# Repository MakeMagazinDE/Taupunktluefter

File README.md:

Maker Media GmbH

***

# Taupunktlüfter

**Lüften ist die beste und billigste Maßnahme gegen feuchte Keller  – jedenfalls, wenn man es richtig macht und sich nicht von außen zusätzliche Nässe ins Gewölbe holt. Bei unserem Projekt behält ein Arduino Nano die aktuellen Taupunkte drinnen und draußen rund um die Uhr im Auge und legt durch gezieltes Lüften den Keller trocken.**

Hier gibt es den Arduino-Code zum Projekt des Taupunktlüfters sowohl in der Fassung ohne Datenlogger (Code im Ordner _Taupunkt_Lueftung_), wie in Make 1/22 beschrieben, als auch in der Fassung mit Datenlogger (Code im Ordner _Taupunkt_Lueftung_Datenlogging_Version_2.13_), die in Make 2/22 beschrieben wird. Diese Version zeigt auch der erweiterte Schaltplan:

Der im Schaltplan gezeigte _Modusschalter_ ist ein Schalter mit drei Schaltstellungen: links, Mitte, rechts. In der Mittelstellung sind alle Pole frei, bei rechts wird der mittlere Pol nach rechts verbunden und bei links der mittlere Pol nach links. Beschaltet wird dann beispielsweise so: linker Kontakt des Schalters auf GND (linke Stellung ist dann für **aus**), rechter Kontakt auf VCC (5V, rechte Stellung ist dann für **an**) und Mittelkontakt auf Arduino-IO-Pin 6 (Verbindung zum Relais, Mittelstellung ist dann für **Automatik**).

Die wichtigsten Fragen rund um den Taupunktlüfter beantwortet eine **[FAQ](https://heise.de/-6526328)**. Die vollständigen Artikel zum Projekt gibt es in der **[Make-Ausgabe 1/22 ab Seite 22](https://www.heise.de/select/make/2022/1/2135511212557842576)** und in der **[Make-Ausgabe 2/22 ab Seite 82](https://www.heise.de/select/make/2022/2/2204711461516715363)** zu lesen.

Dank Patrick alias _resipat265_ aus dem heise-Forum gibt es jetzt auch eine Vorlage für den Nachbau auf **[Lochraster-Platine](./Lochraster/Lochraster.md)**. Vielen Dank dafür!

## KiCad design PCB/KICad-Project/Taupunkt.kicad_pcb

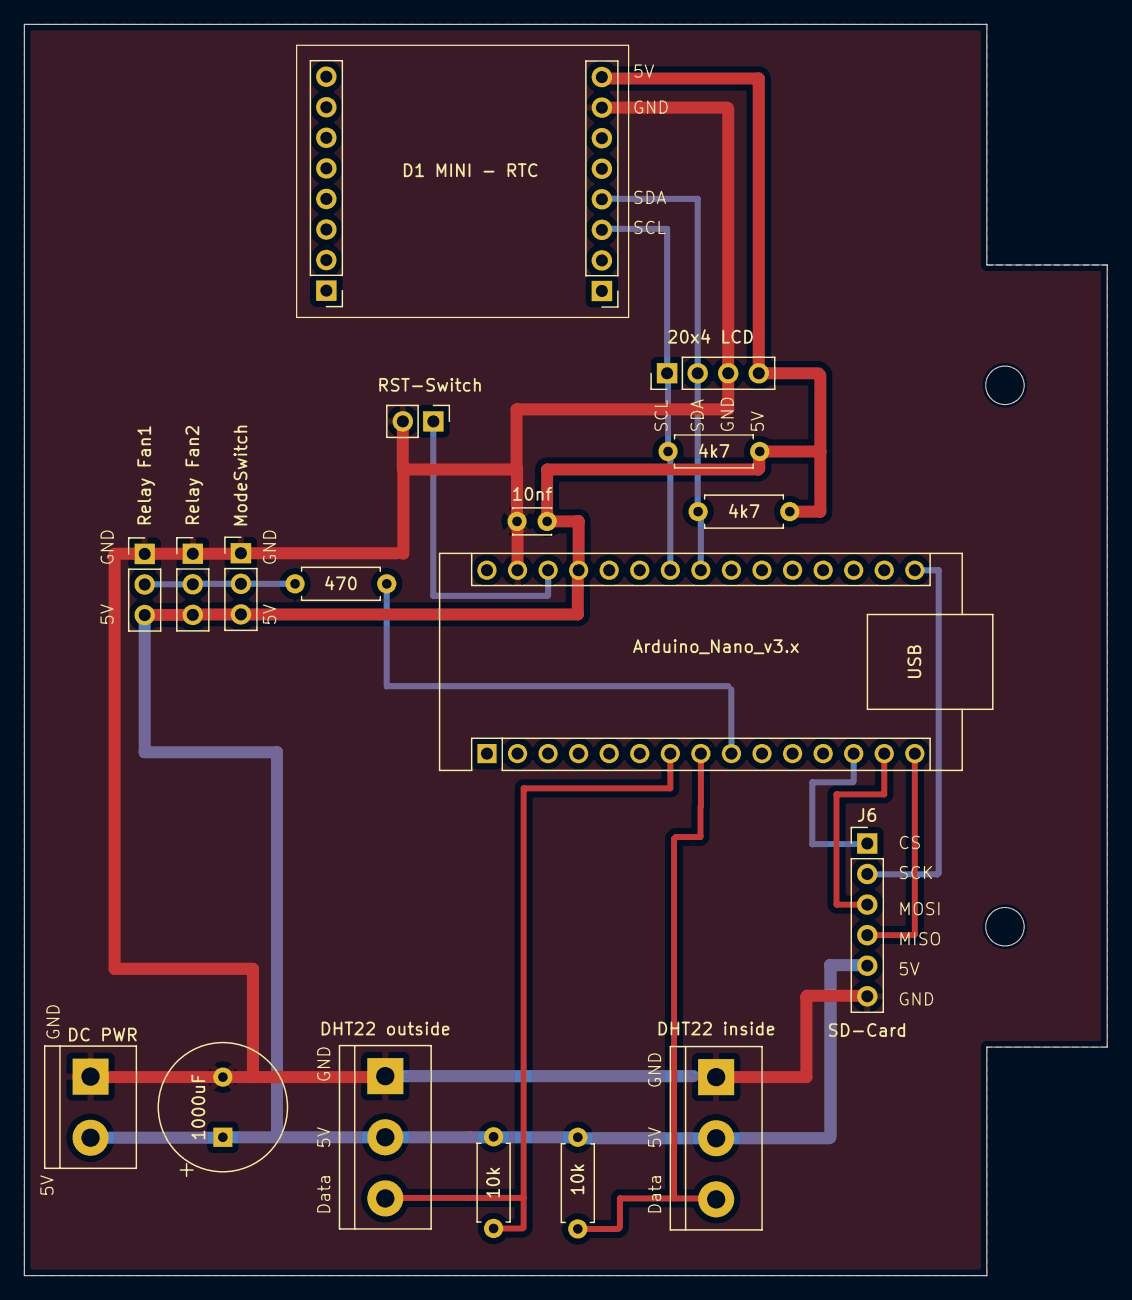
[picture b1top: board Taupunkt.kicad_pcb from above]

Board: 2 copper layers, 90.0 x 104.0 mm, 19 parts (0 on the bottom side), 12 nets.

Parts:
A1: Arduino_Nano_v3.x; Arduino_Nano
C1: 1000uF; CP_Radial_Tantal_D10.5mm_P5.00mm
C2: 10nf; C_Disc_D3.0mm_W2.0mm_P2.50mm
J1: DC PWR; TerminalBlock_bornier-2_P5.08mm
J2: DHT22 outside; TerminalBlock_bornier-3_P5.08mm
J3: DHT22 inside; TerminalBlock_bornier-3_P5.08mm
J4: 20x4 LCD; PinHeader_1x04_P2.54mm_Vertical
J5, J5#2: D1 MINI - RTC; PinHeader_1x08_P2.54mm_Vertical
J6: SD-Card; PinHeader_1x06_P2.54mm_Vertical
J7: Relay Fan2; PinHeader_1x03_P2.54mm_Vertical
J7#2: Relay Fan1; PinHeader_1x03_P2.54mm_Vertical
R1, R2: 10k; R_Axial_DIN0207_L6.3mm_D2.5mm_P7.62mm_Horizontal
R3, R4: 4k7; R_Axial_DIN0207_L6.3mm_D2.5mm_P7.62mm_Horizontal
R5: 470; R_Axial_DIN0207_L6.3mm_D2.5mm_P7.62mm_Horizontal
SW1: RST-Switch; PinHeader_1x02_P2.54mm_Vertical
SW2: ModeSwitch; PinHeader_1x03_P2.54mm_Vertical

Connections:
/<NO NET>: A1.27 (+5V), C1.1, C2.1, J1.2, J2.2, J3.2, J4.4, J5.8, J6.5, J7.3, J7#2.3, R1.1, R2.1, R3.2, R4.2, SW2.3 (4)
/CS: A1.13 (D10), J6.1
/D4 - Data inside: A1.7 (D4), J2.3, R1.2
/D5 - Data outside: A1.8 (D5), J3.3, R2.2
/GND: A1.29 (GND), C1.2, C2.2, J1.1, J2.1, J3.1, J4.3, J5.7, J6.6, J7.1, J7#2.1, SW1.2, SW2.1
/MISO: A1.15 (D12), J6.4
/MOSI: A1.14 (D11), J6.3
/RelSwitch: A1.9 (D6), J7.2, J7#2.2, R5.1, R5.2, SW2.2 (3)
/SCK: A1.16 (D13), J6.2
/SCL: A1.24 (A5), J4.1, J5.3, R3.1
/SDA: A1.23 (A4), J4.2, J5.4, R4.1
unnamed: A1.28 (~RESET), SW1.1

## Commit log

2022-02-26 Add backlight timeout. Switch backlight off after 4 cycles. Can be switch on by trigger of INT0 on PD2.
2022-06-10 +Version 3.00
2022-06-10 ~Header und Version
2022-06-11 +force SD write on fan state change
2022-06-12 New structure
2022-06-15 ~SD header
2022-06-19 ~Correction values
2022-06-22 +Now correctly hold state until limit is reached
2022-06-30 Lochraster-Version hinzugefügt
2022-07-10 removed \r, changed hysteresis, added debug message
2022-07-10 removed typo to correct error with min state hold time
